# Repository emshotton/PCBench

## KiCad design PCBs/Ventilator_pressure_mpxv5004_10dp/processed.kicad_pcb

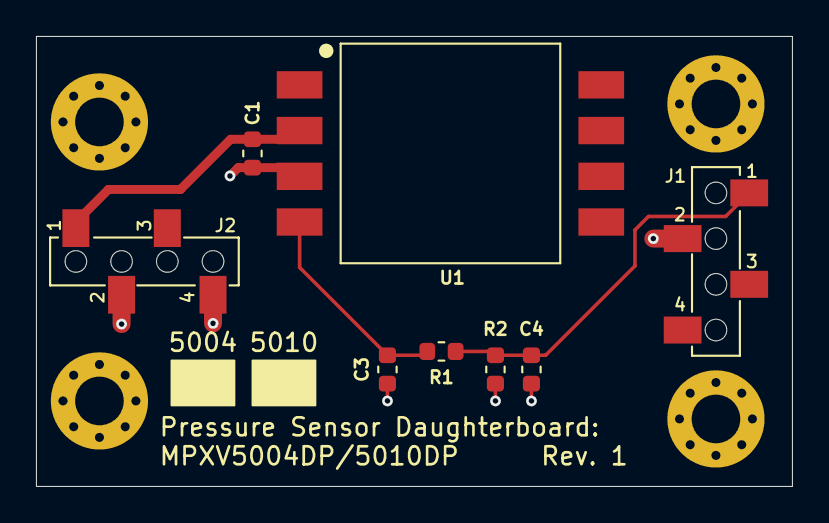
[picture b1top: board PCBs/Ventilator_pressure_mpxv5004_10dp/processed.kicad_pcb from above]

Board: 2 copper layers, 42.0 x 25.0 mm, 12 parts (0 on the bottom side), 4 nets.

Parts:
C1, C4: 1uF; C_0603_1608Metric
C3: 470pF; C_0603_1608Metric
H1, H2, H3, H4: M2.5; MountingHole_2.7mm_M2.5_Pad_Via
J1, J2: Main board connections (bottom entry); PinSocket_1x04_P2.54mm_Vertical_SMD_TE_1241152-4
R1: 2.4K; R_0603_1608Metric
R2: 4.7K; R_0603_1608Metric
U1: MPXV5004DP; NXP_MPXV5004DP

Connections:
+5V_Sns: C1.2, J2.1, U1.2
GND: C1.1, C3.1, C4.1, J1.2, J2.2, J2.4, R2.1, U1.3
unnamed: C3.2, R1.2, U1.4
unnamed: C4.2, J1.1, R1.1, R2.2

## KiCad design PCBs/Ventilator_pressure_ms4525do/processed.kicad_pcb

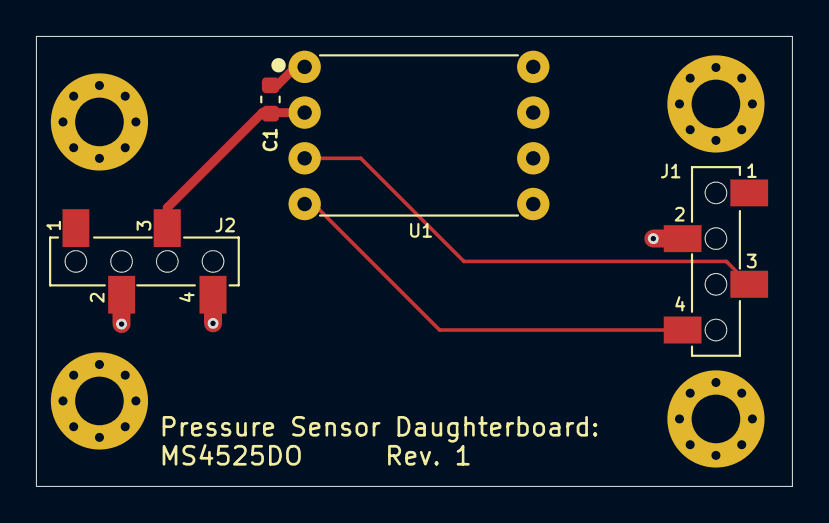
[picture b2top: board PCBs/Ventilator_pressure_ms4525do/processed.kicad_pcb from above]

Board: 2 copper layers, 42.0 x 25.0 mm, 8 parts (0 on the bottom side), 4 nets.

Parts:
C1: 1uF; C_0603_1608Metric
H1, H2, H3, H4: M2.5; MountingHole_2.7mm_M2.5_Pad_Via
J1, J2: Main board connections (bottom entry); PinSocket_1x04_P2.54mm_Vertical_SMD_TE_1241152-4
U1: MS4525DO-DS5AI001DP; TE_MS4525DO-DSxxxxxxDP

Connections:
+3.3V_Sns: C1.2, J2.3, U1.2
/SCL: J1.4, U1.4
/SDA: J1.3, U1.3
GND: C1.1, J1.2, J2.2, J2.4, U1.1

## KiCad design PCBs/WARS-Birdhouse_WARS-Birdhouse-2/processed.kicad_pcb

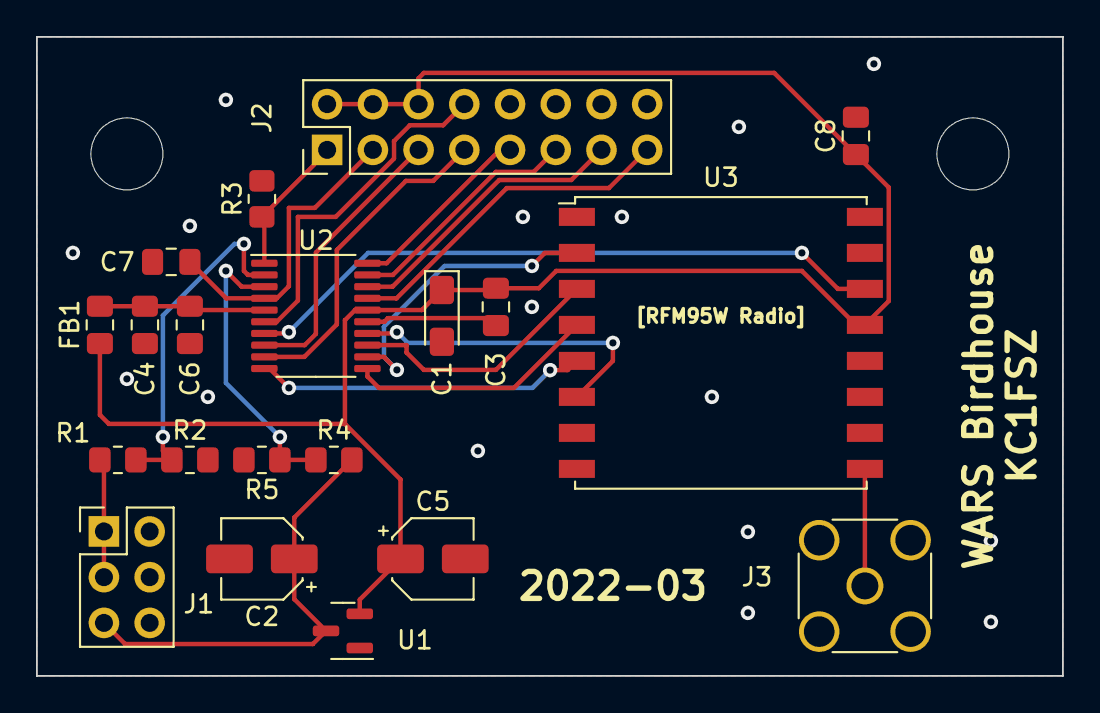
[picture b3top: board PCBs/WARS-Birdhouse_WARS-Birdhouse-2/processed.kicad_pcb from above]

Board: 2 copper layers, 57.0 x 35.5 mm, 22 parts (0 on the bottom side), 23 nets.

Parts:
C1: 10u; CP_EIA-3216-10_Kemet-I_Pad1.58x1.35mm_HandSolder
C2, C5: 10u; CP_Elec_4x5.4
C3, C6, C7, C8: 100n; C_0805_2012Metric_Pad1.18x1.45mm_HandSolder
C4: 1u; C_0805_2012Metric_Pad1.18x1.45mm_HandSolder
FB1: FerriteBead; C_0805_2012Metric_Pad1.18x1.45mm_HandSolder
H1, H2: MountingHole; MountingHole_4mm
J1: Conn_02x03_Odd_Even; PinHeader_2x03_P2.54mm_Vertical
J2: Conn_02x08_Odd_Even; PinHeader_2x08_P2.54mm_Vertical
J3: SMA; SMA_Amphenol_132134_Vertical
R1: 5k; R_0805_2012Metric_Pad1.20x1.40mm_HandSolder
R2, R4, R5: 1k; R_0805_2012Metric_Pad1.20x1.40mm_HandSolder
R3: 10k; R_0805_2012Metric_Pad1.20x1.40mm_HandSolder
U1: MCP1700-3302E_SOT23; SOT-23
U2: STM32L031F6Px; TSSOP-20_4.4x6.5mm_P0.65mm
U3: RFM95W-868S2; HOPERF_RFM9XW_SMD

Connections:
+3V3: C1.1, C3.1, C5.1, C8.1, FB1.1, J2.2, J2.4, J2.6, U1.2 (VO), U2.16 (VDD), U3.13 (3.3V)
BOOT0: J2.1, R3.1, U2.1 (BOOT0)
GND: C1.2, C2.2, C3.2, C4.2, C5.2, C6.2, C7.2, C8.2, J1.2, J1.4, J1.6, J2.10, J2.12, J2.14, J2.16, J3.2 (Ext), R2.2, R3.2, R5.2, U1.1 (GND), U2.15 (VSS), U3.1 (GND), U3.8 (GND), U3.10 (GND)
I2C1_CLK: J2.15, U2.17 (PA9)
I2C1_SDA: J2.13, U2.18 (PA10)
LED0: J2.8, U2.6 (PA0)
NRST: C7.1, J2.3, U2.4 (NRST)
unnamed: J3.1 (In), U3.9 (ANT)
unnamed: U2.14 (PB1), U3.6 (RESET)
RADIO_INT: U2.7 (PA1), U3.14 (DIO0)
RADIO_MISO: U2.12 (PA6), U3.2 (MISO)
RADIO_MOSI: U2.13 (PA7), U3.3 (MOSI)
RADIO_NSS: U2.10 (PA4), U3.5 (NSS)
RADIO_SCK: U2.11 (PA5), U3.4 (SCK)
SWDCLK: J2.9, U2.20 (PA14)
SWDIO: J2.11, U2.19 (PA13)
USART2_RX: J2.7, U2.9 (PA3)
USART2_TX: J2.5, U2.8 (PA2)
VDDA: C4.1, C6.1, FB1.2, U2.5 (VDDA)
VPANEL: J1.1, J1.3, R1.2
VPANEL_SENSE: R1.1, R2.1, U2.2 (PC14)
VSUPPLY: C2.1, J1.5, R4.2, U1.3 (VI)
VSUPPLY_SENSE: R4.1, R5.1, U2.3 (PC15)

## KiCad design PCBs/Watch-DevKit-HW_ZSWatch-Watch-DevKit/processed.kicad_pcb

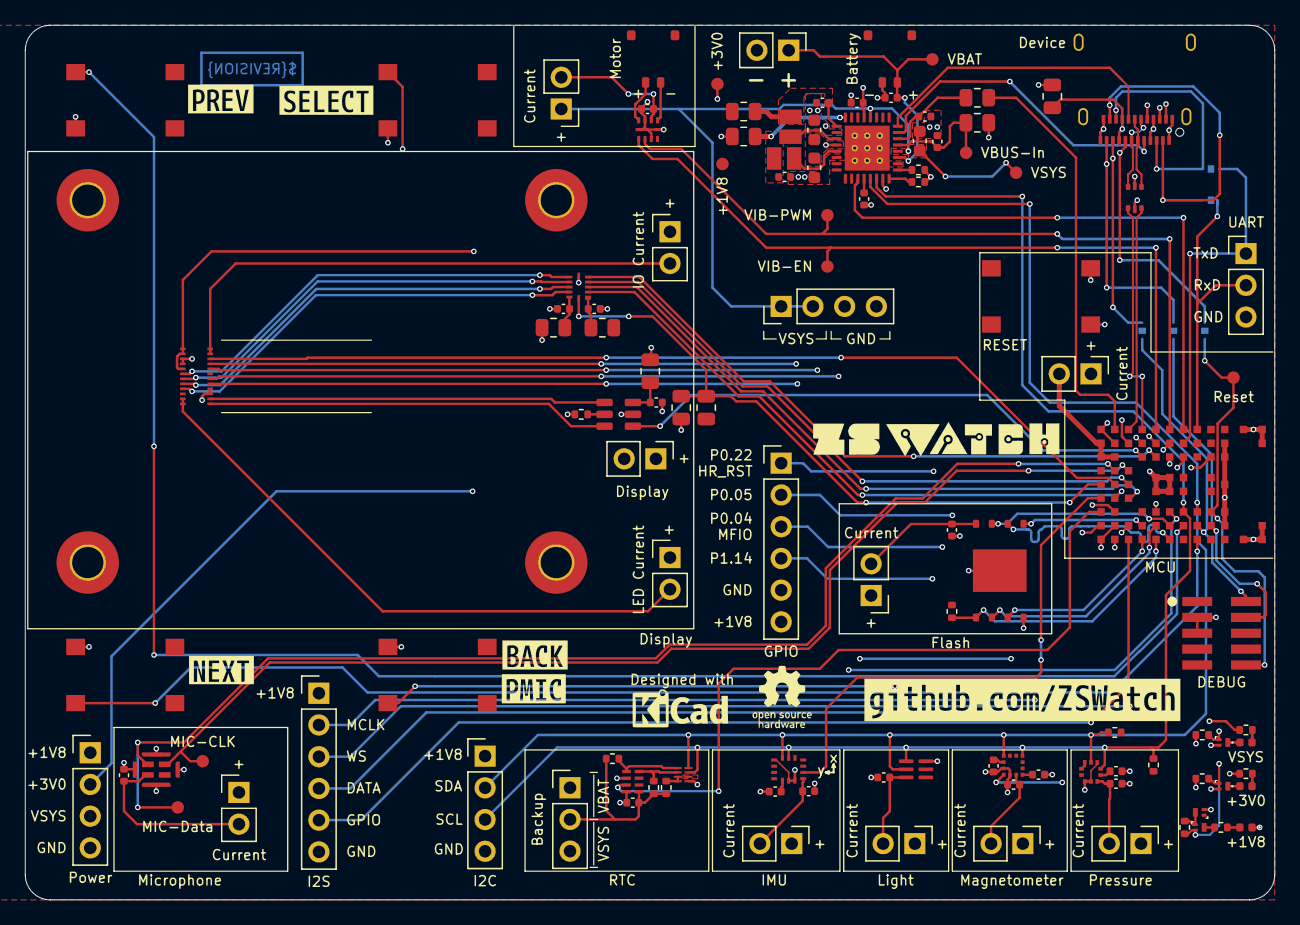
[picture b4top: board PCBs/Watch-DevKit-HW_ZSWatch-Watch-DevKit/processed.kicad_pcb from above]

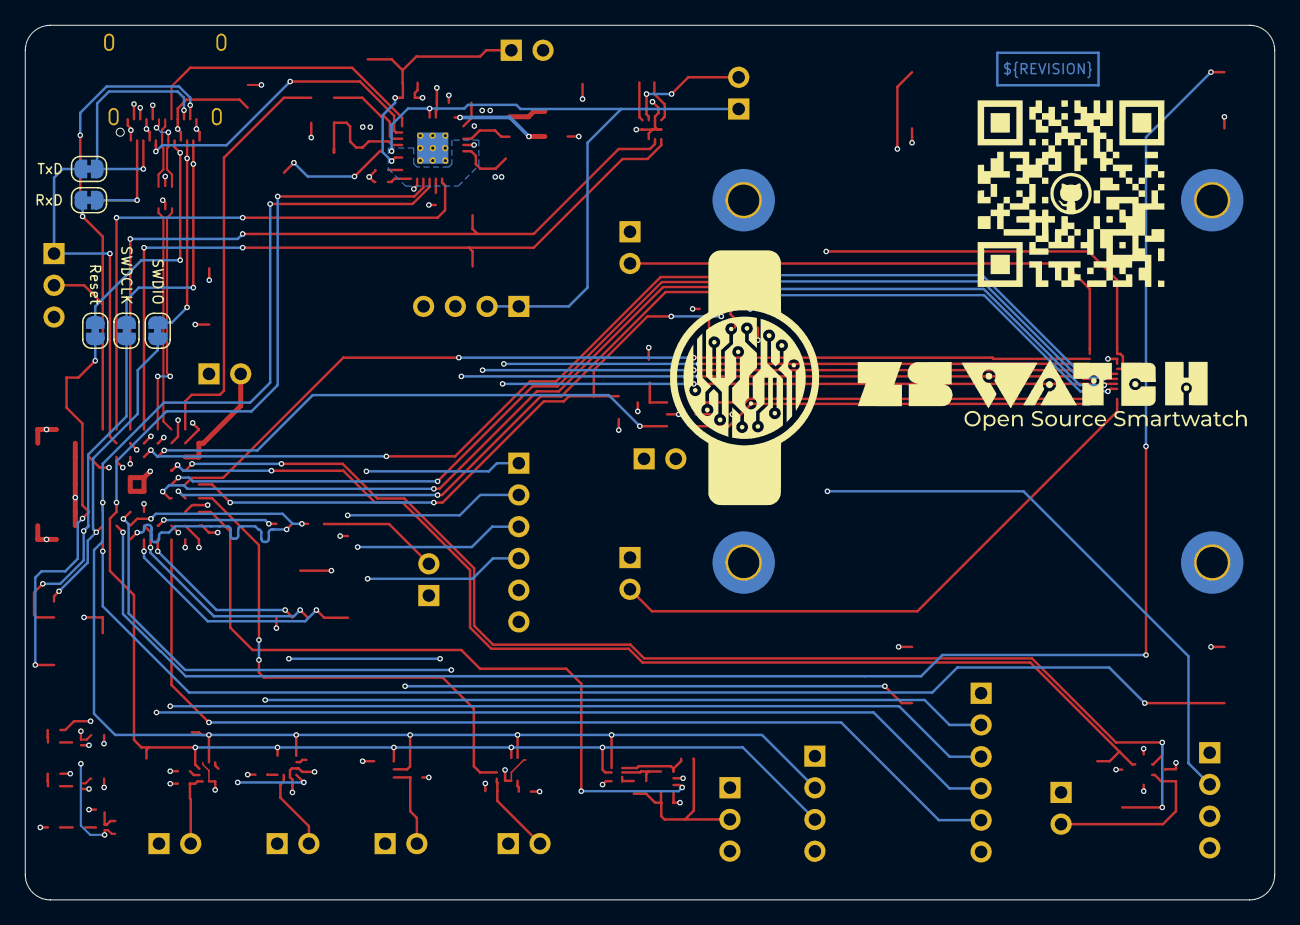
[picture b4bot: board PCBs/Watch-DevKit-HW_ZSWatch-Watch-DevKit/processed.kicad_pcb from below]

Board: 4 copper layers, 100.0 x 70.0 mm, 123 parts (5 on the bottom side), 107 nets.

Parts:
C401, C405, C601: 1u; C_0402_1005Metric
C402, C501, C502, C503, C504, C507, C508, C509, C510, C511, C602, C603, C604: 100n; C_0402_1005Metric
C403: 2u2; C_0402_1005Metric
C404, C406, C408, C506: 10u; C_0402_1005Metric
C407, C409, C410: 10u; C_0603_1608Metric
C505: 220n; C_0402_1005Metric
D401: +3V0; LED_0402_1005Metric
D402: VSYS; LED_0402_1005Metric
D403: +1V8; LED_0402_1005Metric
IC401: nPM1300-QEXX; QFN-32-1EP_5x5mm_P0.5mm_EP3.6x3.6mm_ThermalVias
IC501: APDS-9306-065; Broadcom_DFN-6_2x2mm_P0.65mm
IC502: BMI270; Bosch_LGA-14_3x2.5mm_P0.5mm_LayoutBorder3x4y
IC503: LIS2MDLTR; LGA-12_2x2mm_P0.5mm
IC504: BMP581; Bosch_LGA-10_2x2mm_P0.5mm_ClockwisePinNumbering
IC505: DRV2603RUNT; WQFN-10_2x2mm_P0.5mm
IC506: PCA9306JK; XSON-8_0.65x0.17mm_P0.35mm
IC507: RV-8263-C8
IC601: FAN5622SX; TSOT-23-6
IC602: USBLC6-2P6; SOT-666
IC603: MX25U51245GZ4I00; WSON-8-1EP_8x6mm_P1.27mm_EP3.4x4.3mm
IC604: NTS0104GU12; XQFN-12-1.7x2mm_P0.4mm
JP601: SWDIO; SolderJumper-2_P1.3mm_Bridged_RoundedPad1.0x1.5mm
JP602: SWDCLK; SolderJumper-2_P1.3mm_Bridged_RoundedPad1.0x1.5mm
JP603: Reset; SolderJumper-2_P1.3mm_Bridged_RoundedPad1.0x1.5mm
JP604: TxD; SolderJumper-2_P1.3mm_Bridged_RoundedPad1.0x1.5mm
JP605: RxD; SolderJumper-2_P1.3mm_Bridged_RoundedPad1.0x1.5mm
L401, L402: 2u2; L_0806_2016
M601: NORA-B106
MK501: SPK0641HT4H-1
Q401, Q402, Q403: PMZ550UNEYL; DFN-1006-3
Q404: PMZB320UPEYL; DFN-1006-3
R401, R402, R403, R408, R612: 100k; R_0402_1005Metric
R404, R405, R406: 560R; R_0402_1005Metric
R407: 47k; R_0402_1005Metric
R409, R410, R411, R412, R602, R603, R615, R616: 0R; R_0805_2012Metric
R501, R502: 1k8; R_0402_1005Metric
R503: 200k; R_0402_1005Metric
R504, R505: 3k3; R_0402_1005Metric
R601: 12k; R_0402_1005Metric
R613, R614: 100k; R_0805_2012Metric
S501: SW1; WS-TASV-6x6
S502: SW2; WS-TASV-6x6
S503: SW3; WS-TASV-6x6
S504: SW4; WS-TASV-6x6
S601: RESET; WS-TASV-6x6
TP401: VBUS-In; TestPoint_Pad_D1.0mm
TP402: VBAT; TestPoint_Pad_D1.0mm
TP403: VSYS; TestPoint_Pad_D1.0mm
TP404: +1V8; TestPoint_Pad_D1.0mm
TP405: +3V0; TestPoint_Pad_D1.0mm
TP501: MIC-CLK; TestPoint_Pad_D1.0mm
TP502: MIC-Data; TestPoint_Pad_D1.0mm
TP503: VIB-EN; TestPoint_Pad_D1.0mm
TP504: VIB-PWM; TestPoint_Pad_D1.0mm
TP601: Reset; TestPoint_Pad_D1.0mm
X401: Battery; PinHeader_1x02_P2.54mm_Vertical
X402: Battery; 78171-0002
X403: Power; PinHeader_1x04_P2.54mm_Vertical
X404: VSYS; PinHeader_1x04_P2.54mm_Vertical
X501, X503, X505, X506, X507, X508, X602, X606: Current; PinHeader_1x02_P2.54mm_Vertical
X502: I2S; PinHeader_1x06_P2.54mm_Vertical
X504: I2C; PinHeader_1x04_P2.54mm_Vertical
X509: Motor; 78171-0002
X510: Current; PinHeader_1x03_P2.54mm_Vertical
X601: DEBUG; SHF-105-01-L-D-SM-TR
X603: Device; USB_C_Receptacle_Amphenol_12401610E4-2A
X604: UART; PinHeader_1x03_P2.54mm_Vertical
X605: GPIO; PinHeader_1x06_P2.54mm_Vertical
X607: IO Current; PinHeader_1x02_P2.54mm_Vertical
X608: Display; ER-CON0.4-24P
X609: Display; PinHeader_1x02_P2.54mm_Vertical
X610: LED Current; PinHeader_1x02_P2.54mm_Vertical
kibuzzard-683075F5: G***; kibuzzard-683075F5
kibuzzard-691724A3: G***; kibuzzard-691724A3
kibuzzard-691724A9: G***; kibuzzard-691724A9
kibuzzard-6830428E: G***; kibuzzard-6830428E
kibuzzard-68303879: G***; kibuzzard-68303879
kibuzzard-68304289: G***; kibuzzard-68304289

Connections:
+1V8: C402.1, C503.1, C506.1, C508.2, IC401.12 (V_{IO}), IC502.5 (VDDIO), IC502.12 (CSB), IC503.3 (CS), IC503.10 (VDDIO), IC504.1 (VDDIO), IC504.5 (SDO), IC504.6 (CSB), IC506.2 (VCC_{1}), MK501.3 (SEL), Q401.G, R410.1, R501.2, R502.2, R612.1, R613.2, R615.2, TP404.1, X403.1, X501.1, X502.1, X504.1, X505.1, X506.1, X507.1, X601.1 (VTref), X602.1, X605.6, X606.1, X607.1
+3V0: R404.2, R411.1, R602.1, R616.2, TP405.1, X403.2, X609.1, X610.1
/Project Architecture/MCU/BMI270-INT: IC502.9 (INT2), M601.A4 (P1.00)
/Project Architecture/MCU/D+: IC602.1 (I/O1), X603.A6 (D+), X603.B6 (D+)
/Project Architecture/MCU/D-: IC602.3 (I/O2), X603.A7 (D-), X603.B7 (D-)
/Project Architecture/MCU/Data: M601.J7 (P1.10), X502.4
/Project Architecture/MCU/GPIO: M601.C1 (P0.10/TRACEDATA[1]), X502.5
/Project Architecture/MCU/LIS2MDL-INT: IC503.7 (INT/DRDY), M601.E3 (P0.21)
/Project Architecture/MCU/MCLK: M601.F7 (P1.07), X502.2
/Project Architecture/MCU/MIC-CLK: M601.C6 (P0.00/XL1), MK501.2 (CLK), TP501.1
/Project Architecture/MCU/MIC-DATA: M601.B6 (P0.01/XL2), MK501.1 (DATA), TP502.1
/Project Architecture/MCU/PMIC-INT: IC401.11 (GPIO4), M601.G9 (P1.13)
/Project Architecture/MCU/SCL: IC401.14 (SCL), IC501.1 (SCL), IC502.13 (SCK), IC503.1 (SCL/SPC), IC504.2 (SCK), IC506.3 (SCL_{1}), M601.G3 (P0.25/AIN4), R501.1, X504.3
/Project Architecture/MCU/SDA: IC401.13 (SDA), IC501.2 (SDA), IC502.14 (SDI), IC503.4 (SDA/SDI/SDO), IC504.4 (SDI), IC506.4 (SDA_{1}), M601.H3 (P0.27/AIN6), R502.1, X504.2
/Project Architecture/MCU/SW1: M601.F3 (P0.19), S501.1
/Project Architecture/MCU/SW2: IC401.15 (SHPHLD), S502.2
/Project Architecture/MCU/SW3: M601.H1 (P0.24), S503.2
/Project Architecture/MCU/SW4: M601.G2 (P0.26/AIN5), S504.1
/Project Architecture/MCU/USB-CC1: IC401.23 (CC1), X603.A5 (CC1)
/Project Architecture/MCU/USB-CC2: IC401.24 (CC2), X603.B5 (CC2)
/Project Architecture/MCU/USB-VBUS-In: IC602.5 (VBUS), Q402.G, Q403.G, Q404.S, R401.1, R402.1, R403.1, R409.1, R603.2
/Project Architecture/MCU/USB-VBUS-Out: M601.B9 (VBUS), R412.2
/Project Architecture/MCU/VIB-EN: IC505.1 (EN), M601.E9 (P1.05), TP503.1
/Project Architecture/MCU/VIB-PWM: IC505.2 (PWM), M601.F9 (P1.15), TP504.1
/Project Architecture/MCU/WS: M601.G7 (P1.09), X502.3
/Project Architecture/MCU/~RTC-INT: IC507.3 (~INT), M601.A3 (P1.03/I2C)
/Project Architecture/Peripherals/VBAT: C403.1, IC401.19 (V_{BAT}), TP402.1, X401.1, X402.1, X510.1
/Project Architecture/Peripherals/VMIC: C404.1, IC401.29 (LSOUT1/VOUTLDO1), X503.1
/Project Architecture/Power Management/VBUS-In: C401.1, IC401.21 (V_{BUS}), R409.2, TP401.1
/Project Architecture/Power Management/VSYS: C407.1, C409.1, C410.1, IC401.4 (V_{DD}), IC401.20 (V_{SYS}), IC401.28 (LSIN1/VINLDO1), R405.2, TP403.1, X403.3, X404.1, X404.2, X508.1, X510.3
DISPLAY-BLK: IC601.1 (CTRL), M601.D7 (P0.23)
DISPLAY-CLK: M601.B1 (P0.08/TRACEDATA[3]), X608.8 (SCL)
DISPLAY-CS: M601.B3 (P0.11/TRACEDATA[0]), X608.9 (CS)
DISPLAY-DATA: M601.C2 (P0.09/TRACEDATA[2]), X608.6 (SDI/SDA)
DISPLAY-DC: M601.A2 (P0.12/TRACECLK), X608.5 (RS/DC)
DISPLAY-RST: M601.B5 (P0.03/NFC2), X608.10 (RESET)
GND: C401.2, C402.2, C403.2, C404.2, C405.2, C406.2, C407.2, C408.2, C409.2, C410.2, C501.2, C502.2, C503.2, C504.1, C505.2, C506.2, C507.2, C508.1, C509.2, C510.2, C511.2, C601.1, C602.1, C603.2, C604.2, D403.1 (K), IC401.2 (PVSS1), IC401.6 (PVSS2), IC401.18 (NTC), IC401.33 (GND), IC501.6 (GND), IC502.1 (SDO), IC502.6 (GND), IC502.7 (GND), IC503.6 (GND), IC503.8 (GND), IC504.3 (GND), IC504.8 (GND), IC504.9 (GND), IC505.3 (LRA/~ERM), IC505.5 (GND), IC505.8 (GND), IC505.10 (GND), IC506.1 (GND), IC507.2 (CLKOE), IC507.4 (GND), IC601.2 (GND), IC602.2 (GND), IC603.4 (GND), IC603.9 (EP), IC604.6 (GND), M601.A1 (GND), M601.A9 (GND), M601.B2 (GND), M601.B8 (GND), M601.E4 (GND), M601.E5 (GND), M601.F4 (GND), M601.F5 (GND), M601.K2 (GND), M601.K3 (GND), M601.K5 (GND), M601.K7 (GND), M601.K8 (GND), M601.L1 (GND), M601.L9 (GND), M601.M1 (GND), M601.M2 (GND), M601.M8 (GND), M601.M9 (GND), MK501.5 (GND), MK501.6 (GND), MK501.7 (GND), MK501.8 (GND), Q401.S, Q402.S, Q403.S, R401.2, R402.2, R407.1, R408.1, R601.1, R614.1, S501.2, S502.1, S503.1, S504.2, S601.2, X401.2, X402.2, X403.4, X404.3, X404.4, X502.6, X504.4, X601.3 (GND), X601.5 (GND), X603.A1 (GND), X603.A12 (GND), X603.B1 (GND), X603.B12 (GND), X603.S1 (SHIELD), X604.3, X605.5, X608.3 (GND), X608.4 (GND), X608.15 (GND), X608.16 (GND)
LEDK1: IC601.6 (LED1), X608.1 (LEDK-1)
LEDK2: IC601.4 (LED2), X608.2 (LEDK-2)
unnamed: D401.2 (A), R404.1
unnamed: D401.1 (K), Q402.D
unnamed: D402.2 (A), R405.1
unnamed: D402.1 (K), Q403.D
unnamed: D403.2 (A), R406.1
unnamed: IC401.3 (SW1), L402.2
unnamed: IC401.5 (SW2), L401.2
unnamed: C405.1, IC401.22 (VBUS_{OUT}), R412.1
unnamed: C408.1, IC401.1 (VOUT1), L402.1, R410.2
unnamed: C406.1, IC401.32 (VOUT2), L401.1, R411.2
unnamed: IC401.17 (VSET1), R407.2
unnamed: IC401.16 (VSET2), R408.2
unnamed: C501.1, IC501.3 (VDD), X501.2
unnamed: C504.2, IC502.8 (VDD), X505.2
unnamed: C505.1, IC503.5 (C1)
unnamed: C507.1, IC503.9 (VDD), X506.2
unnamed: C509.1, IC504.10 (VDD), X507.2
unnamed: IC505.9 (OUT+), X509.2
unnamed: IC505.6 (OUT-), X509.1
unnamed: C510.1, IC505.7 (VDD), X508.2
unnamed: IC506.7 (VCC_{2}), IC506.8 (EN), R503.2
unnamed: IC506.6 (SCL_{2}), IC507.8 (SCL), R504.1
unnamed: IC506.5 (SDA_{2}), IC507.1 (SDA), R505.1
unnamed: C511.1, IC507.5 (V_{DD}), R503.1, R504.2, R505.2, X510.2
unnamed: IC601.5 (ISET), R601.2
unnamed: C601.2, IC601.3 (VIN), R602.2
unnamed: C602.2, IC603.8 (VCC), X606.2
unnamed: IC604.10 (B1), X608.21 (CTP-INT)
unnamed: IC604.9 (B2), X608.20 (CTP-SCL)
unnamed: IC604.8 (B3), X608.19 (CTP-SDA)
unnamed: IC604.7 (B4), X608.18 (CTP-RST)
unnamed: C603.1, IC604.1 (VCCA), R615.1
unnamed: C604.1, IC604.11 (VCCB), R616.1
unnamed: JP601.1 (A), X603.A10 (RX2-), X603.B10 (RX1-)
unnamed: JP602.1 (A), X603.A11 (RX2+), X603.B11 (RX1+)
unnamed: JP603.1 (A), X603.A8 (SBU1), X603.B8 (SBU2)
unnamed: JP604.1 (A), X603.A3 (TX1-), X603.B3 (TX2-)
unnamed: JP605.1 (A), X603.A2 (TX1+), X603.B2 (TX2+)
unnamed: M601.A7 (VDD), M601.A8 (VDDH), M601.B7 (VDD), X602.2
unnamed: M601.D8 (P0.04/AIN0), X605.3
unnamed: M601.E8 (P0.05/AIN1), X605.2
unnamed: M601.C8 (P0.22), X605.1
unnamed: M601.F8 (P1.14), X605.4
unnamed: C502.1, MK501.4 (VDD), X503.2
unnamed: Q401.D, Q404.G, R403.2
unnamed: Q404.D, R406.2
unnamed: R603.1, X603.A4 (VBUS), X603.A9 (VBUS), X603.B4 (VBUS), X603.B9 (VBUS)
unnamed: X607.2, X608.11 (VDDIO), X608.12 (VDDIO)
unnamed: X608.13 (VDD), X608.14 (VDD), X608.17 (CTP-VDD), X609.2
unnamed: X608.23 (LEDA2), X608.24 (LEDA1), X610.2
QSPI-CLK: IC603.6 (SCK), M601.F1 (P0.17/QSPI_CLK)
QSPI-CS: IC603.1 (~CS), M601.E1 (P0.18/QSPI_CS), R612.2
QSPI-IO0: IC603.5 (SI(I/O0)), M601.D2 (P0.13/QSPI[0])
QSPI-IO1: IC603.2 (SO(I/O1)), M601.E2 (P0.14/QSPI[1])
QSPI-IO2: IC603.3 (~WP(I/O2)), M601.D1 (P0.15/QSPI[2])
QSPI-IO3: IC603.7 (~HOLD(I/O3)), M601.F2 (P0.16/QSPI[3])
RESETn: JP603.2 (B), M601.J3 (~RESET), S601.1, TP601.1, X601.10 (~RESET)
RxD: JP605.2 (B), M601.H9 (P1.11), X604.2
SWDCLK: JP602.2 (B), M601.J2 (SWDCLK), X601.4 (SWCLK/TCK)
SWDIO: JP601.2 (B), M601.H2 (SWDIO), X601.2 (SWDIO/TMS)
TOUCH-EN: IC604.12 (OE), M601.A5 (P0.20), R613.1, R614.2
TOUCH-INT: IC604.2 (A1), M601.B4 (P1.02/I2C)
TOUCH-RST: IC604.5 (A4), M601.E7 (P0.06/AIN2)
TOUCH-SCL: IC604.3 (A2), M601.C4 (P1.01)
TOUCH-SDA: IC604.4 (A3), M601.C5 (P0.02/NFC1)
TxD: JP604.2 (B), M601.G8 (P1.12), X604.1
USB-D+: IC602.6 (I/O1), M601.C9 (D+)
USB-D-: IC602.4 (I/O2), M601.D9 (D-)

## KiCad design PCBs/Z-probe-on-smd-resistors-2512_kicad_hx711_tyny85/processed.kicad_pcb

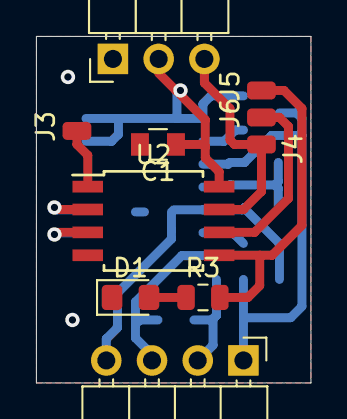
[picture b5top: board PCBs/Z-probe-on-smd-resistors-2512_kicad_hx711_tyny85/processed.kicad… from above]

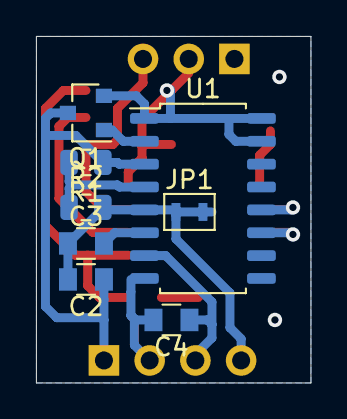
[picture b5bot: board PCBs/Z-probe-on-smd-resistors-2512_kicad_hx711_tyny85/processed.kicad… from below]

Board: 2 copper layers, 15.2 x 19.2 mm, 18 parts (8 on the bottom side), 16 nets.

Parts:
C1: 4.7u; C_0805
C2, C3: 1u; C_0805
C4: 0.1u; C_0805
D1: LED; LED_0805_2012Metric_Pad1.15x1.40mm_HandSolder
J1: Conn_01x03_Male; Pin_Header_Angled_1x03_Pitch2.54mm
J2: Conn_01x04_Female; Pin_Header_Angled_1x04_Pitch2.54mm
J3, J4, J5, J6: Conn_01x01_Female; SMD_wire_conn
JP1: Jumper; AnalogGND_jumper
Q1: Q_PNP_BEC; SOT-23
R1: 22k; R_0805_2012Metric
R2: 8k2; R_0805_2012Metric
R3: 2k2; R_0805_2012Metric
U1: HX711; SOP-16_4.55x10.3mm_P1.27mm
U2: ATtiny85V-10SU; SOIJ-8_5.3x5.3mm_P1.27mm

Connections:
DOUT: U1.12, U2.2
GND: C1.2, D1.1, J1.1, JP1.2, U1.9, U1.10, U1.14, U2.4
GNDA: C2.2, C3.1, J2.4, JP1.1, R2.2, U1.5
INNA: C4.1, J2.3, U1.7
INPA: C4.2, J2.2, U1.8
MISO: J6.1, U2.6
MOSI: J5.1, R3.2, U2.5
unnamed: C3.2, U1.6
unnamed: D1.2, R3.1
unnamed: Q1.1, U1.2
unnamed: R1.2, R2.1, U1.4
RST: J3.1, U2.1
SCK: U1.11, U2.3
SCK_OUT: J1.3, J4.1, U2.7
VCC: C1.1, J1.2, Q1.2, U1.1, U1.15, U1.16, U2.8
VDDA: C2.1, J2.1, Q1.3, R1.1, U1.3
